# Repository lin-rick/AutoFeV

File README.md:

# AutoFeV
Autonomous following electric vehicle using a modified iRobot Roomba and Raspberry Pi.

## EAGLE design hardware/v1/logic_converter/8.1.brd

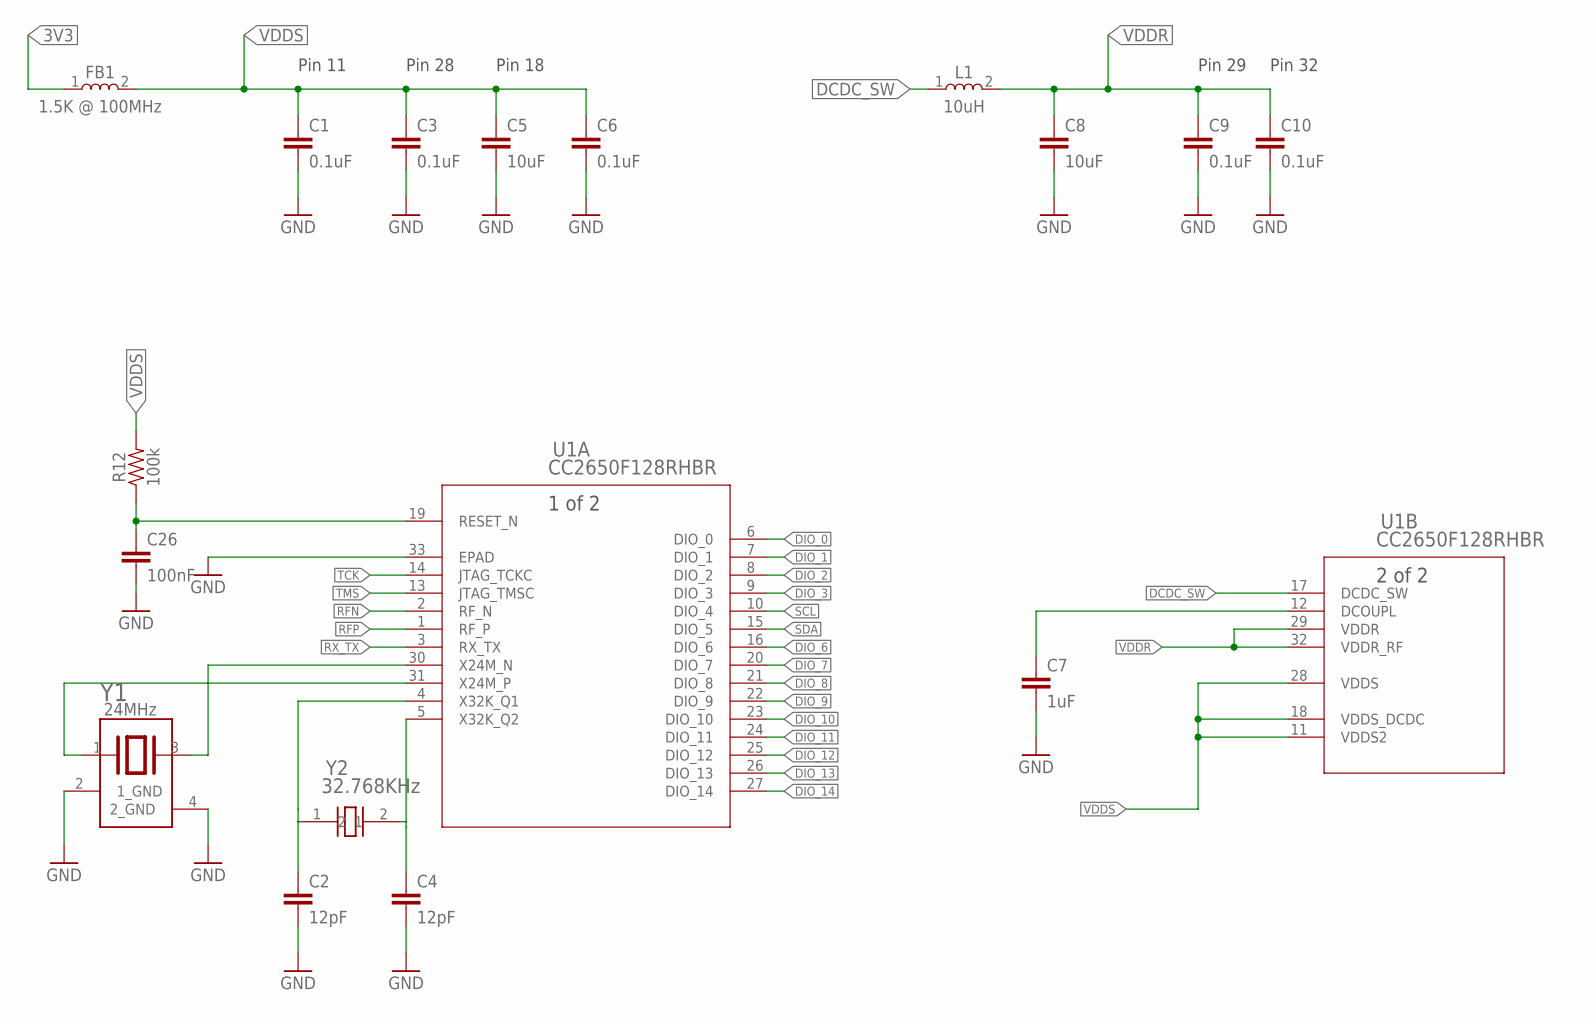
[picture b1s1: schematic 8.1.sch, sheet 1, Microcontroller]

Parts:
C1, C3, C6, C9, C10: 0.1uF; 0402
C2, C4: 12pF; 0402
C5, C8: 10uF; 0402
C7: 1uF; 0402
C26: 100nF; 0402
FB1: 1.5K @ 100MHz; 0603
L1: 10uH; 0805
R12: 100k; 0402; MPN CR0603-JW-103ELF
U1: CC2650F128RHBR; VFQFN-32
Y1: 24MHz; TSX-3225
Y2: 32.768KHz; FC-135

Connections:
3V3: FB1.1; also elsewhere on the board
DCDC_SW: L1.1, U1.17 (DCDC_SW)
DIO_0: U1.6 (DIO_0)
DIO_1: U1.7 (DIO_1)
DIO_2: U1.8 (DIO_2)
DIO_3: U1.9 (DIO_3)
DIO_6: U1.16 (DIO_6)
DIO_7: U1.20 (DIO_7)
DIO_8: U1.21 (DIO_8); also elsewhere on the board
DIO_9: U1.22 (DIO_9); also elsewhere on the board
DIO_10: U1.23 (DIO_10); also elsewhere on the board
DIO_11: U1.24 (DIO_11); also elsewhere on the board
DIO_12: U1.25 (DIO_12); also elsewhere on the board
DIO_13: U1.26 (DIO_13); also elsewhere on the board
DIO_14: U1.27 (DIO_14)
GND: C1.2, C2.2, C3.2, C4.2, C5.2, C6.2, C7.2, C8.2, C9.2, C10.2, C26.2, U1.33 (EPAD), Y1.2 (1_GND), Y1.4 (2_GND); also elsewhere on the board
unnamed: C7.1, U1.12 (DCOUPL)
unnamed: U1.30 (X24M_N), Y1.3
unnamed: U1.31 (X24M_P), Y1.1
unnamed: C2.1, U1.4 (X32K_Q1), Y2.1
unnamed: C4.1, U1.5 (X32K_Q2), Y2.2
unnamed: C26.1, R12.1, U1.19 (RESET_N)
RFN: U1.2 (RF_N); also elsewhere on the board
RFP: U1.1 (RF_P); also elsewhere on the board
RX_TX: U1.3 (RX_TX)
SCL: U1.10 (DIO_4); also elsewhere on the board
SDA: U1.15 (DIO_5); also elsewhere on the board
TCK: U1.14 (JTAG_TCKC); also elsewhere on the board
TMS: U1.13 (JTAG_TMSC); also elsewhere on the board
VDDR: C8.1, C9.1, C10.1, L1.2, U1.29 (VDDR), U1.32 (VDDR_RF)
VDDS: C1.1, C3.1, C5.1, C6.1, FB1.2, R12.2, U1.11 (VDDS2), U1.18 (VDDS_DCDC), U1.28 (VDDS)

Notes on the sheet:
Pin 11
Pin 28
Pin 18
Pin 29
Pin 32

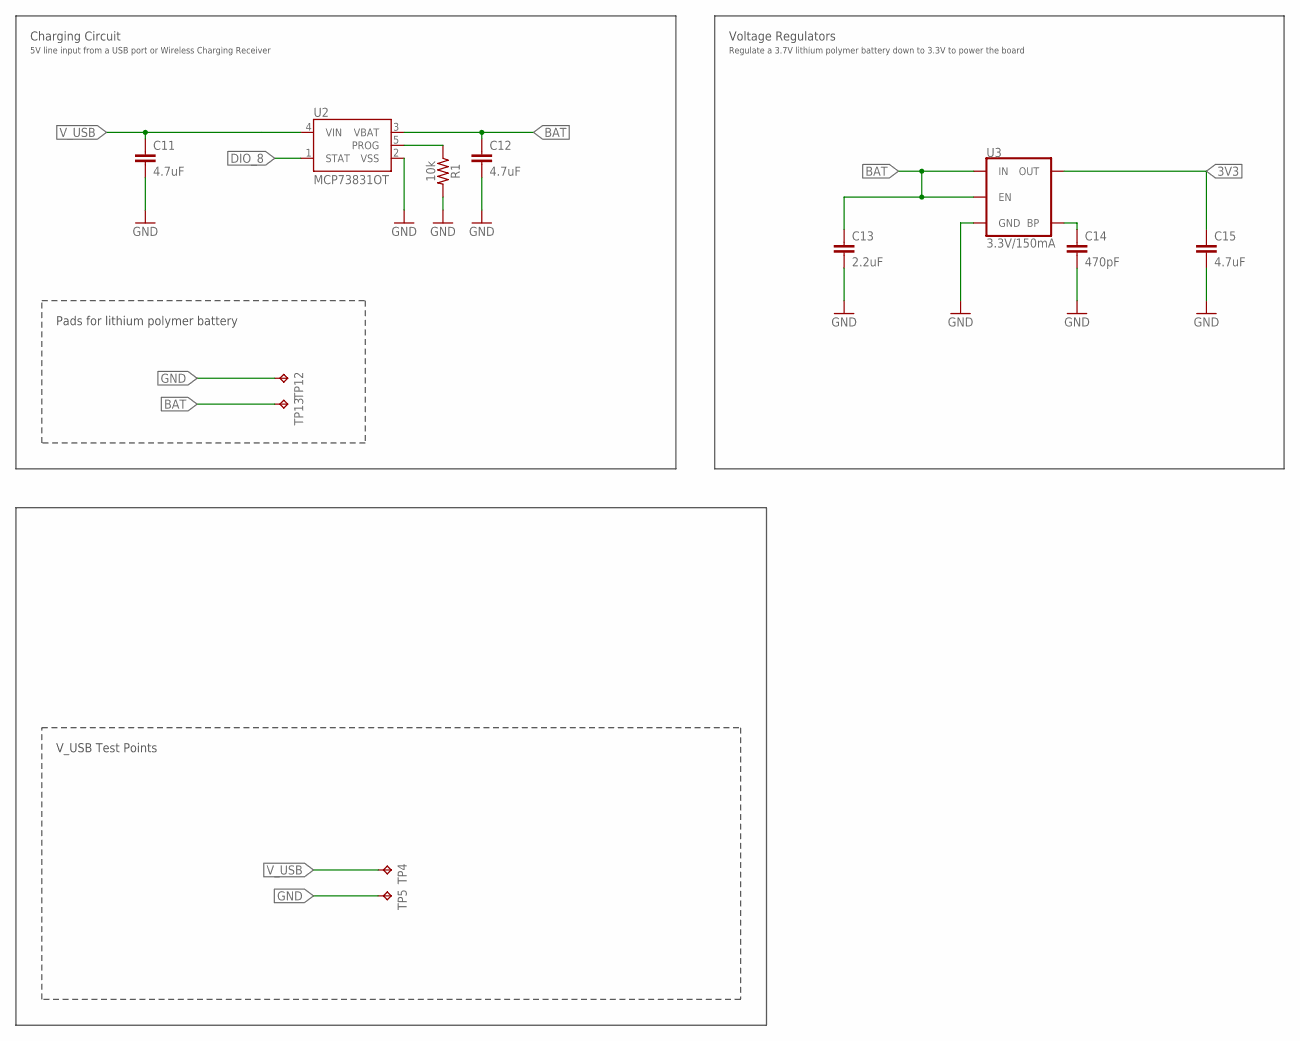
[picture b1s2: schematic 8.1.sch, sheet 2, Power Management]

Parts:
C11, C12: 4.7uF; 0402
C13: 2.2uF; 0402; MPN 0603YC104K4Z2A
C14: 470pF; 0402; MPN 0603YC104K4Z2A
C15: 4.7uF; 0402; MPN 0603YC104K4Z2A
R1: 10k; 0402
TP4, TP5: TESTPADBOTH; TESTPAD_1.27_BOTH_SIDE
TP12, TP13: TESTPAD; WIREPAD_1.27_2.54
U2: MCP73831OT; SOT23-5
U3: 3.3V/150mA; SOT23-5; MPN MIC5205-5.0YM5 TR

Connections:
3V3: C15.1, U3.5 (OUT); also elsewhere on the board
BAT: C12.1, C13.1, TP13.1, U2.3 (VBAT), U3.1 (IN), U3.3 (EN)
DIO_8: U2.1 (STAT); also elsewhere on the board
GND: C11.2, C12.2, C13.2, C14.2, C15.2, R1.2, TP5.P$1, TP5.TP, TP5.TP1, TP12.1, U2.2 (VSS), U3.2 (GND); also elsewhere on the board
unnamed: R1.1, U2.5 (PROG)
unnamed: C14.1, U3.4 (BP)
V_USB: C11.1, TP4.P$1, TP4.TP, TP4.TP1, U2.4 (VIN); also elsewhere on the board

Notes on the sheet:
V_USB Test Points
Voltage Regulators
Pads for lithium polymer battery
Regulate a 3.7V lithium polymer battery down to 3.3V to power the board
Charging Circuit
5V line input from a USB port or Wireless Charging Receiver

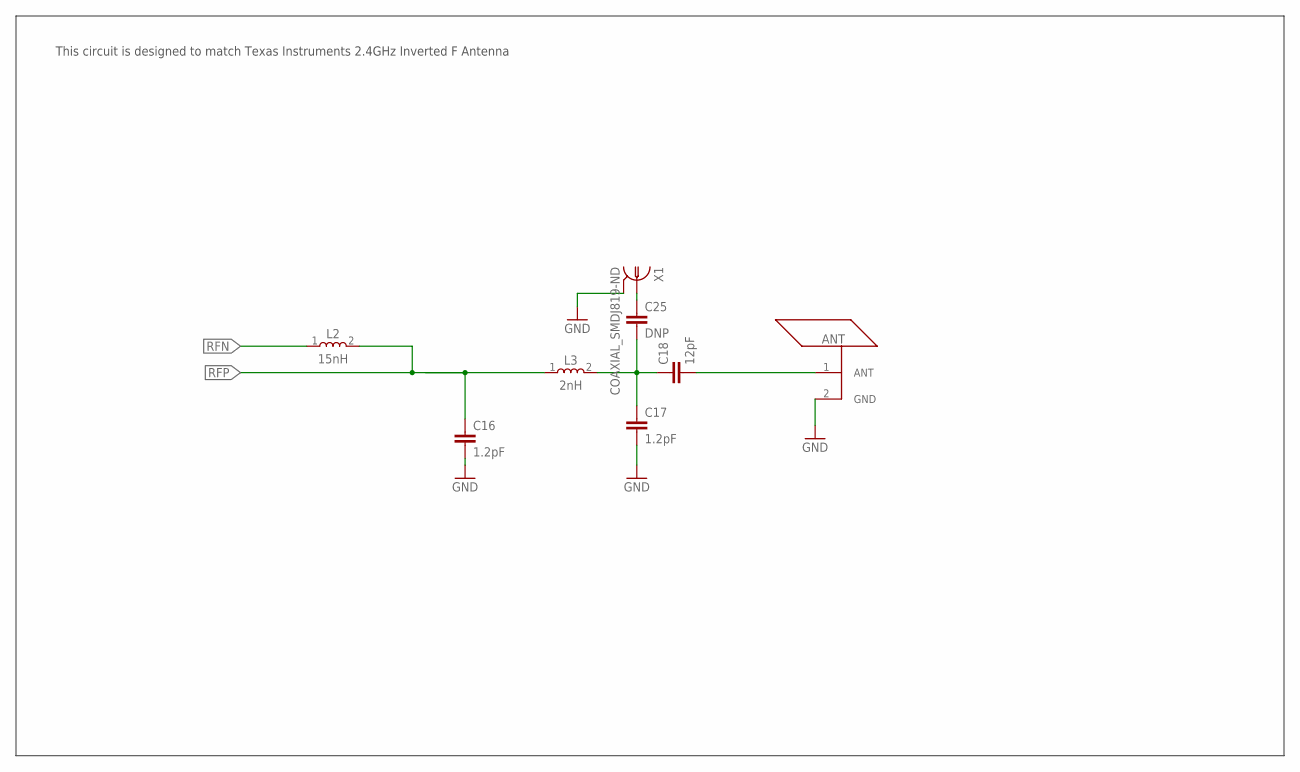
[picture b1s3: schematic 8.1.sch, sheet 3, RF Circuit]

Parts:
ANT: ANT; AN043_ANT_TRACE
C16, C17: 1.2pF; 0402
C18: 12pF; 0402
C25: DNP; 0402
L2: 15nH; 0402
L3: 2nH; 0402
X1: COAXIAL_SMDJ819-ND; COAXIAL_SMD

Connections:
GND: ANT.2 (GND), C16.2, C17.2, X1.2@1 (2), X1.2@2 (2), X1.2@3 (2), X1.2@4 (2), X1.2@5 (2), X1.2@6 (2); also elsewhere on the board
unnamed: C17.1, C18.1, C25.2, L3.2
unnamed: ANT.1 (ANT), C18.2
unnamed: C25.1, X1.1
RFN: L2.1; also elsewhere on the board
RFP: C16.1, L2.2, L3.1; also elsewhere on the board

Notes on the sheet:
This circuit is designed to match Texas Instruments 2.4GHz Inverted F Antenna

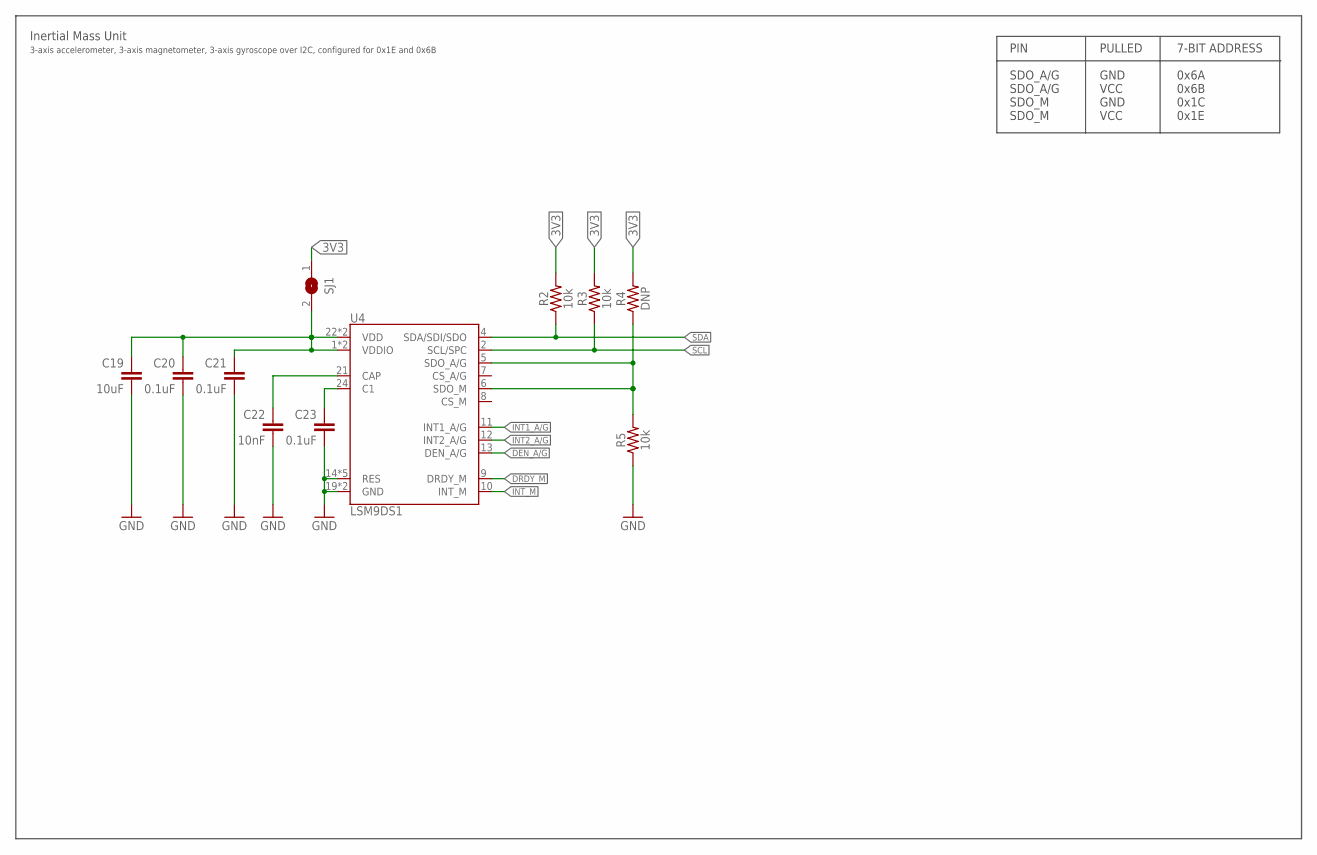
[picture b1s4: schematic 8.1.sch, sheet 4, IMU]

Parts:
C19: 10uF; 0402
C20, C21, C23: 0.1uF; 0402
C22: 10nF; 0402
R2, R3, R5: 10k; 0402; MPN CR0603-JW-103ELF
R4: DNP; 0402; MPN CR0603-JW-103ELF
SJ1: SOLDER_JUMPER
U4: LSM9DS1; LGA-24

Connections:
3V3: R2.2, R3.2, R4.2, SJ1.1; also elsewhere on the board
C1: C23.1, U4.24 (C1)
CAP: C22.1, U4.21 (CAP)
DEN_A/G: U4.13 (DEN_A/G)
DRDY_M: U4.9 (DRDY_M)
GND: C19.2, C20.2, C21.2, C22.2, C23.2, R5.1, U4.14 (RES), U4.15 (RES), U4.16 (RES), U4.17 (RES), U4.18 (RES), U4.19 (GND), U4.20 (GND); also elsewhere on the board
IMU_VDD: C19.1, C20.1, C21.1, SJ1.2, U4.1 (VDDIO), U4.3 (VDDIO), U4.22 (VDD), U4.23 (VDD)
INT1_A/G: U4.11 (INT1_A/G)
INT2_A/G: U4.12 (INT2_A/G)
INT_M: U4.10 (INT_M)
SCL: R3.1, U4.2 (SCL/SPC); also elsewhere on the board
SDA: R2.1, U4.4 (SDA/SDI/SDO); also elsewhere on the board
SDO: R4.1, R5.2, U4.5 (SDO_A/G), U4.6 (SDO_M)

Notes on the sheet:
Inertial Mass Unit
3-axis accelerometer, 3-axis magnetometer, 3-axis gyroscope over I2C, configured for 0x1E and 0x6B
PIN SDO_A/G SDO_A/G SDO_M SDO_M
PULLED GND VCC GND VCC
7-BIT ADDRESS 0x6A 0x6B 0x1C 0x1E

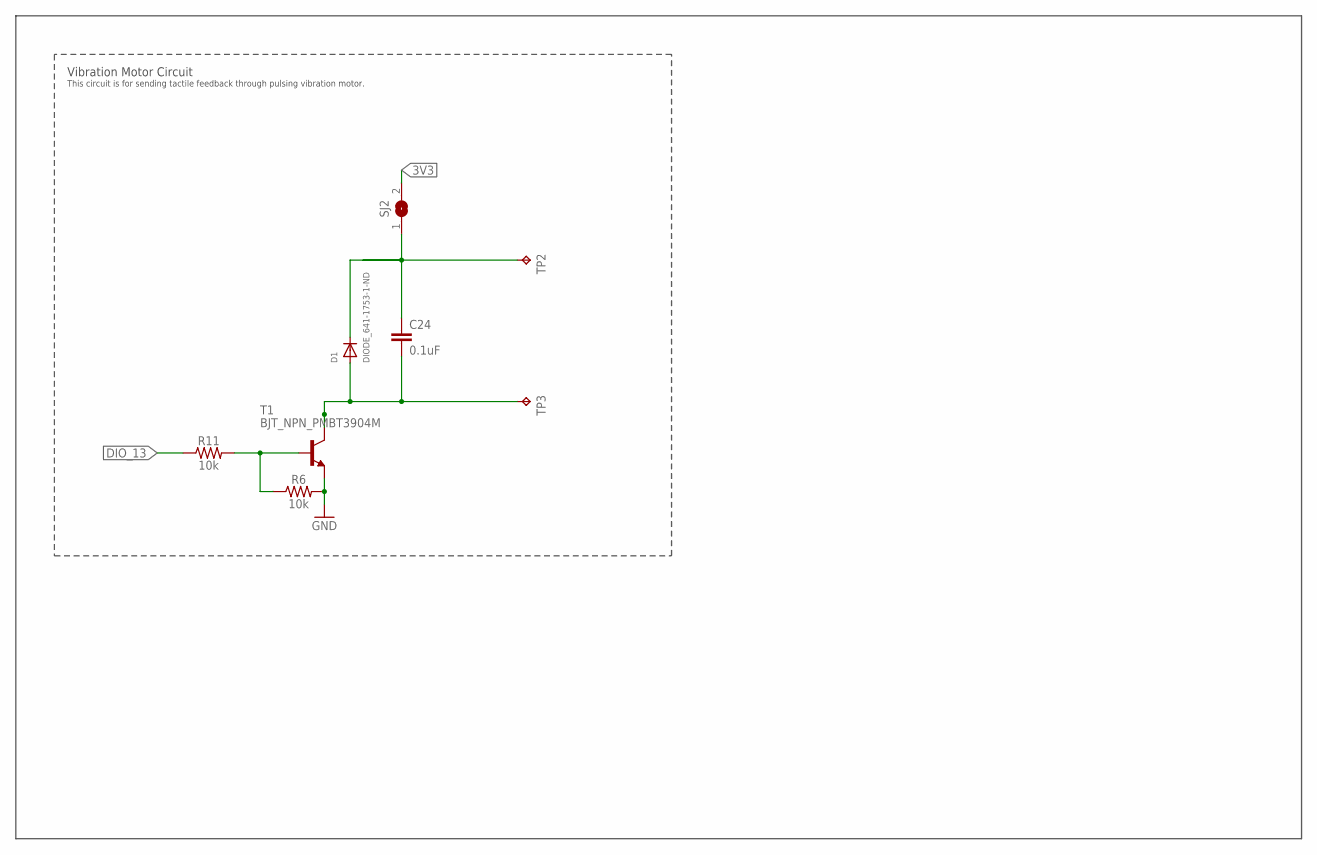
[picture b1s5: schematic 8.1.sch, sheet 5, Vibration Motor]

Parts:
C24: 0.1uF; 0402
D1: DIODE_641-1753-1-ND; SOD-923F
R6, R11: 10k; 0402
SJ2: SOLDER_JUMPER
T1: BJT_NPN_PMBT3904M; SOT-883
TP2, TP3: TESTPADBOTH; TESTPAD_1.27_BOTH_SIDE

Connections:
3V3: SJ2.2; also elsewhere on the board
DIO_13: R11.1; also elsewhere on the board
GND: R6.2, T1.2 (E); also elsewhere on the board
MOTOR_VDD: C24.1, D1.C, SJ2.1, TP2.P$1, TP2.TP, TP2.TP1
unnamed: C24.2, D1.A, T1.3 (C), TP3.P$1, TP3.TP, TP3.TP1
unnamed: R6.1, R11.2, T1.1 (B)

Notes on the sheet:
This circuit is for sending tactile feedback through pulsing vibration motor.
Vibration Motor Circuit

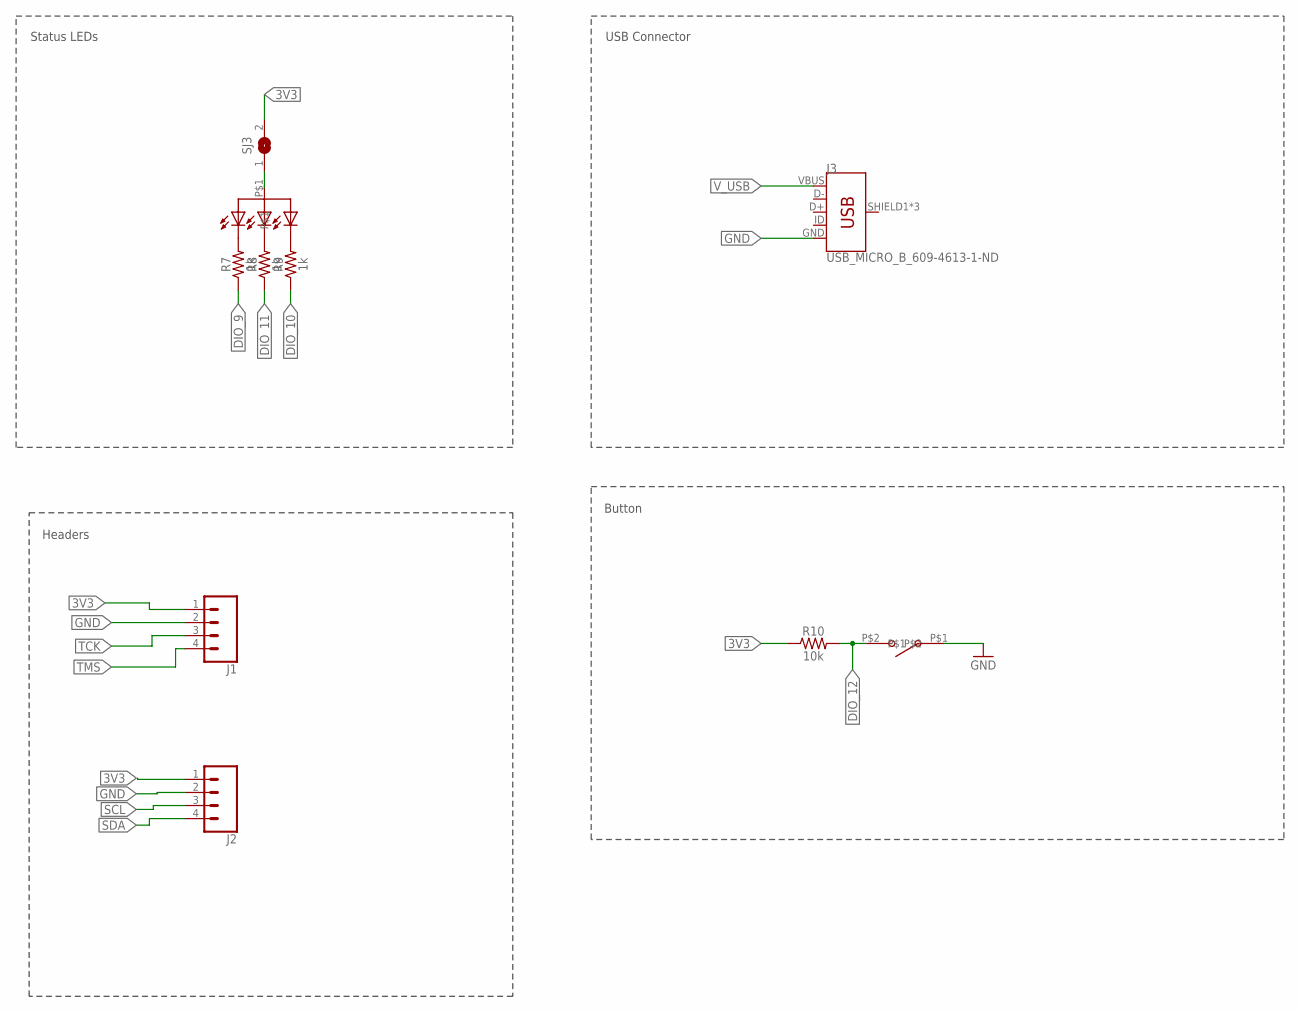
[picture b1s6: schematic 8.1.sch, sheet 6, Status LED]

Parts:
J1, J2: CONN_04; 1X04
J3: USB_MICRO_B_609-4613-1-ND; USB_MICRO_B
LED1: LED_TRICOLOR_3.2X2.8; LED_3.2X2.8
R7, R8, R9: 1k; 0402
R10: 10k; 0402
SJ3: SOLDER_JUMPER
SW1: TACTILE_SWITCHES_CKN10839CT-ND; PTS820_J25M

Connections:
3V3: J1.1, J2.1, R10.1, SJ3.2; also elsewhere on the board
DIO_9: R7.1; also elsewhere on the board
DIO_10: R9.1; also elsewhere on the board
DIO_11: R8.1; also elsewhere on the board
DIO_12: R10.2, SW1.P$2; also elsewhere on the board
GND: J1.2, J2.2, J3.GND, SW1.P$1; also elsewhere on the board
unnamed: LED1.P$2, R7.2
unnamed: LED1.P$3, R8.2
unnamed: LED1.P$4, R9.2
unnamed: LED1.P$1, SJ3.1
SCL: J2.3; also elsewhere on the board
SDA: J2.4; also elsewhere on the board
TCK: J1.3; also elsewhere on the board
TMS: J1.4; also elsewhere on the board
V_USB: J3.VBUS; also elsewhere on the board

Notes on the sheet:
Status LEDs
USB Connector
Headers
Button

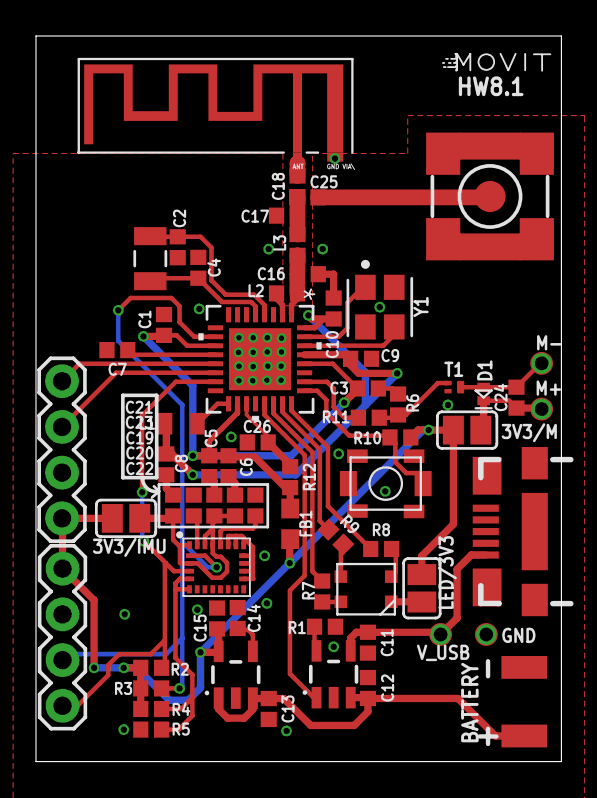
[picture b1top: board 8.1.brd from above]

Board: 2 copper layers, 29.2 x 40.3 mm, 66 parts (0 on the bottom side), 41 nets.

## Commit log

2019-05-07 Working. Issues with high delay and steering overshoot
2019-05-07 Deleting placeholder files
2019-08-08 Transferring final version from bitbucket

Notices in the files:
parts and their libraries:
SparkFun-Connectors: Licensing: Creative Commons ShareAlike 4.0 International - https://creativecommons.org/licenses/by-sa/4.0
